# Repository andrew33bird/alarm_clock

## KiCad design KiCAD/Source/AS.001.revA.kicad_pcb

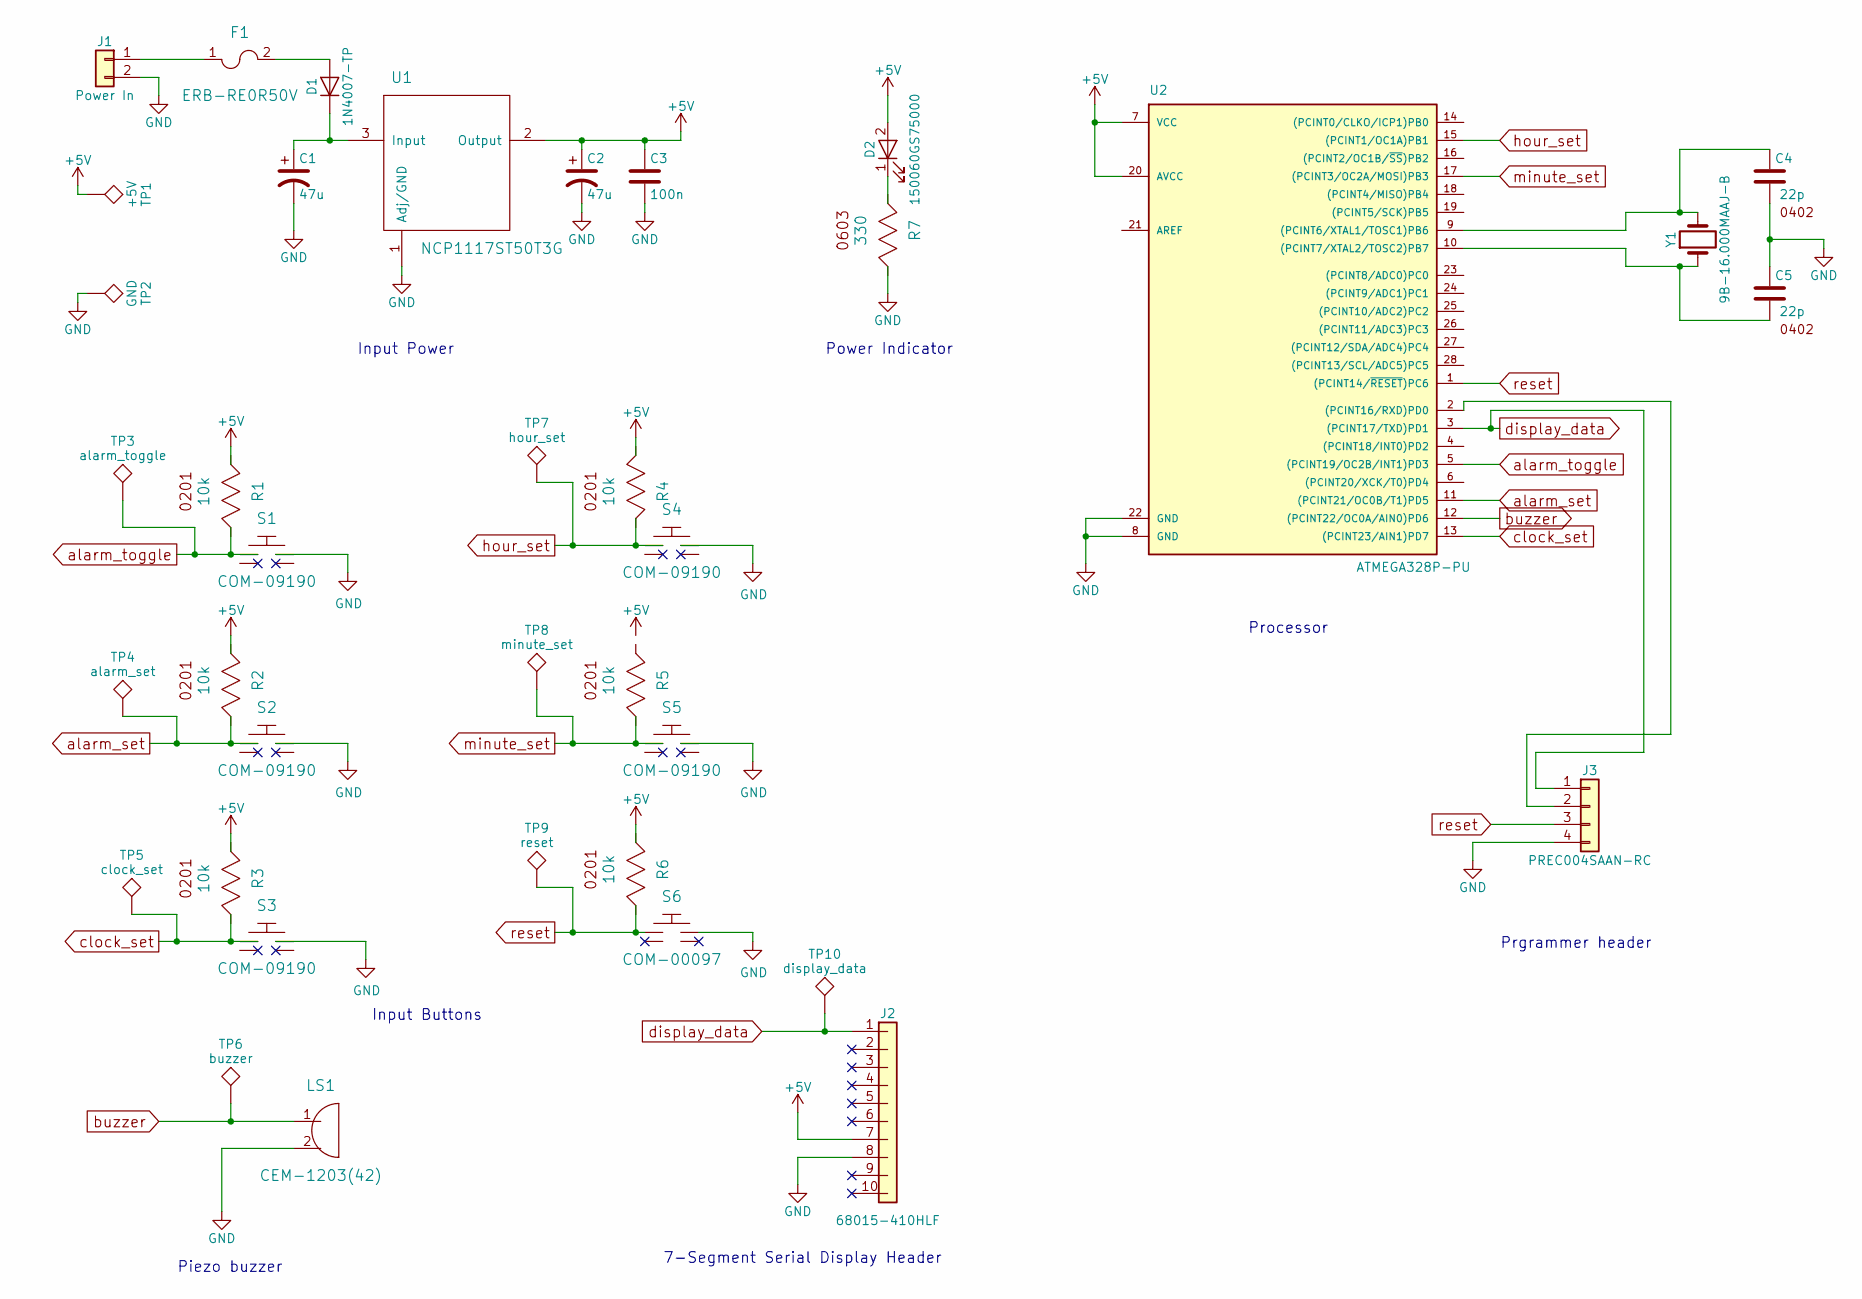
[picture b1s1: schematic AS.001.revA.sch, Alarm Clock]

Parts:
C1, C2: 47u; CP_Radial_D5.0mm_P2.00mm
C3: 100n; C_0603_1608Metric_Pad1.05x0.95mm_HandSolder
C4, C5: 22p; C_0603_1608Metric_Pad1.05x0.95mm_HandSolder
D1: 1N4007-TP; D_DO-41_SOD81_P10.16mm_Horizontal
D2: 150060GS75000; LED_0603_1608Metric_Pad1.05x0.95mm_HandSolder
F1: ERB-RE0R50V; R_0603_1608Metric_Pad1.05x0.95mm_HandSolder
J1: Power In; PinSocket_1x02_P2.54mm_Vertical
J2: 68015-410HLF; PinSocket_1x10_P2.54mm_Horizontal
J3: PREC004SAAN-RC; PinSocket_1x04_P2.54mm_Vertical
LS1: CEM-1203(42)
R1, R2, R3, R4, R5, R6: 10k; R_0603_1608Metric_Pad1.05x0.95mm_HandSolder
R7: 330; R_0603_1608Metric_Pad1.05x0.95mm_HandSolder
S1, S2, S3, S4, S5: COM-09190
S6: COM-00097
TP1: +5V; TestPoint_Plated_Hole_D2.0mm
TP2: GND; TestPoint_Plated_Hole_D2.0mm
TP3: alarm_toggle; TestPoint_Plated_Hole_D2.0mm
TP4: alarm_set; TestPoint_Plated_Hole_D2.0mm
TP5: clock_set; TestPoint_Plated_Hole_D2.0mm
TP6: buzzer; TestPoint_Plated_Hole_D2.0mm
TP7: hour_set; TestPoint_Plated_Hole_D2.0mm
TP8: minute_set; TestPoint_Plated_Hole_D2.0mm
TP9: reset; TestPoint_Plated_Hole_D2.0mm
TP10: display_data; TestPoint_Plated_Hole_D2.0mm
U1: NCP1117ST50T3G; NCP1117ST50T3G (TO-261-4)
U2: ATMEGA328P-PU; DIP-28_W7.62mm
Y1: 9B-16.000MAAJ-B; Crystal_HC49-U_Vertical

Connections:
+5V: C2.1, C3.1, D2.2 (A), J2.7, R1.1 (A), R2.1 (A), R3.1 (A), R4.2 (B), R6.1 (A), TP1.1, U1.2 (Output), U2.7 (VCC), U2.20 (AVCC); also elsewhere on the board
GND: C1.2, C2.2, C3.2, C4.2, C5.1, J1.2, J2.8, J3.4, LS1.2, R7.2 (B), S1.3 (C), S2.3 (C), S3.3 (C), S4.3 (C), S5.3 (C), S6.3 (C), TP2.1, U1.1 (Adj/GND), U2.8 (GND), U2.22 (GND); also elsewhere on the board
unnamed: C1.1, D1.1 (K), U1.3 (Input)
unnamed: C4.1, U2.9 ((PCINT6/XTAL1/TOSC1)PB6), Y1.2
unnamed: C5.2, U2.10 ((PCINT7/XTAL2/TOSC2)PB7), Y1.1
unnamed: D1.2 (A), F1.2
unnamed: D2.1 (K), R7.1 (A)
unnamed: F1.1, J1.1
unnamed: J3.2, U2.2 ((PCINT16/RXD)PD0)
alarm_set: R2.2 (B), S2.1 (A), TP4.1, U2.11 ((PCINT21/OC0B/T1)PD5)
alarm_toggle: R1.2 (B), S1.1 (A), TP3.1, U2.5 ((PCINT19/OC2B/INT1)PD3)
buzzer: LS1.1, TP6.1, U2.12 ((PCINT22/OC0A/AIN0)PD6)
clock_set: R3.2 (B), S3.1 (A), TP5.1, U2.13 ((PCINT23/AIN1)PD7)
display_data: J2.1, J3.1, TP10.1, U2.3 ((PCINT17/TXD)PD1)
hour_set: R4.1 (A), S4.1 (A), TP7.1, U2.15 ((PCINT1/OC1A)PB1)
minute_set: R5.2 (B), S5.1 (A), TP8.1, U2.17 ((PCINT3/OC2A/MOSI)PB3)
reset: J3.3, R6.2 (B), S6.1 (A), TP9.1, U2.1 ((PCINT14/~RESET~)PC6)

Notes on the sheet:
Input Power
Input Buttons
Power Indicator
Piezo buzzer
7-Segment Serial Display Header
Processor
Prgrammer header

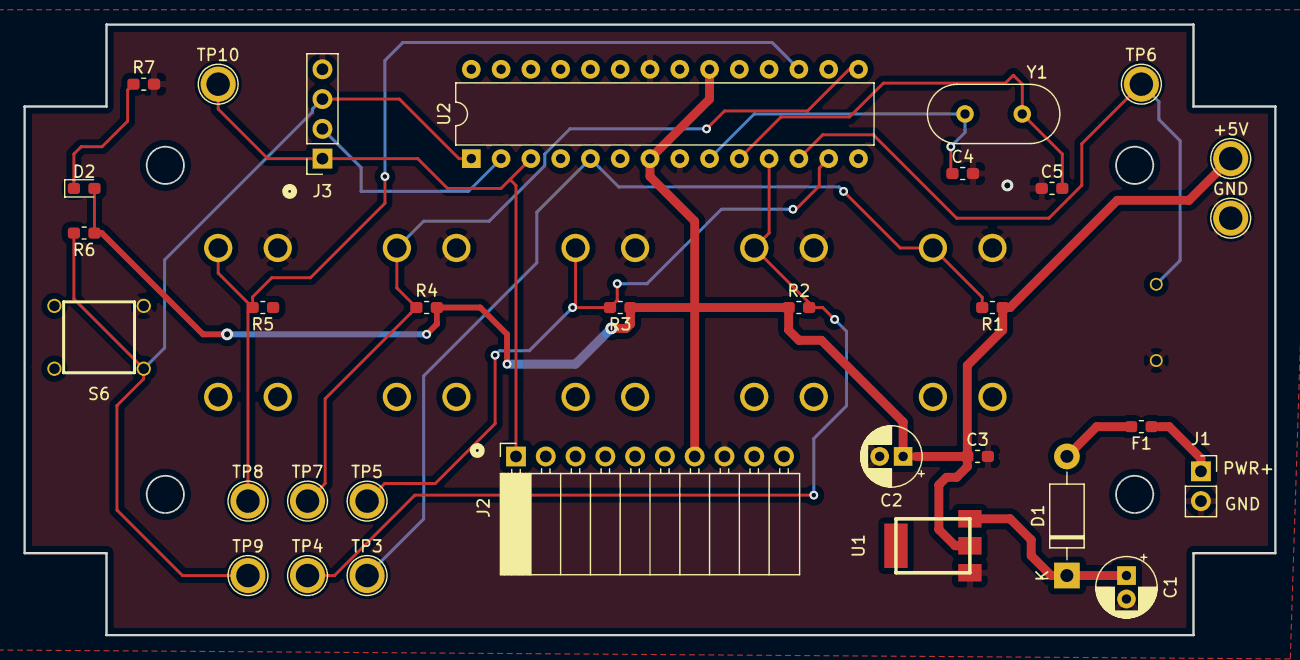
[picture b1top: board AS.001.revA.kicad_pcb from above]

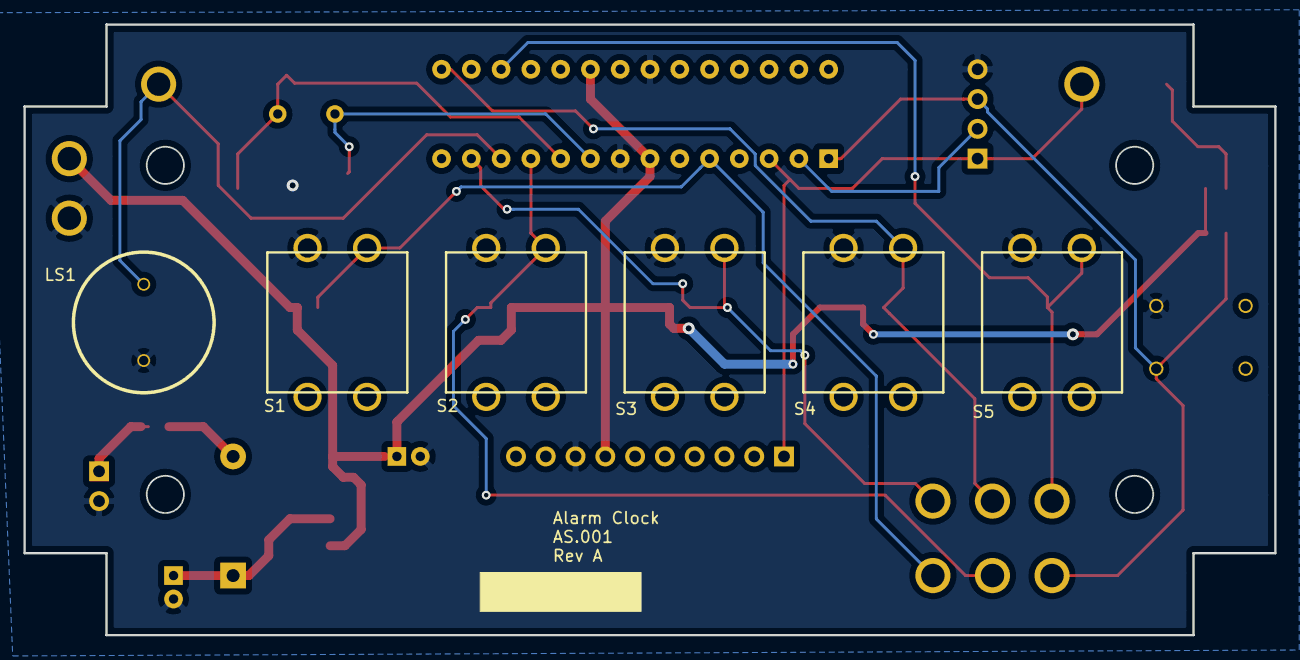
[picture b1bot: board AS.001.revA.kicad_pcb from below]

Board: 2 copper layers, 106.7 x 52.1 mm, 38 parts (6 on the bottom side), 17 nets.

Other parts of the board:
+5V: +5V; TestPoint_Plated_Hole_D2.0mm
GND: GND; TestPoint_Plated_Hole_D2.0mm

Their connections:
+5V: +5V.1; also elsewhere on the board
GND: GND.1; also elsewhere on the board

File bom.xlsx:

Item | Part Number | Qnty | Price (ea) | Price (tot) | Distributor | Link
Microcontroller | ATMEGA328P-PU | 1 | 2.6 | 2.6 | Amazon | https://www.amazon.com/gp/product/B07BZMCK8S/ref=oh_aui_deta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
5V Regulator | NCP1117ST50T3G | 1 | 0.54 | 0.54 | Digikey | https://www.digikey.com/product-detail/en/on-semiconductor/N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
47 uF Capacitor | 860020472006 | 2 | 0.1 | 0.2 | Digikey | https://www.digikey.com/product-detail/en/wurth-electronics-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
Power Diode | 1N4007-TP | 1 | 0.11 | 0.11 | Digikey | https://www.digikey.com/product-detail/en/micro-commercial-c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
100 nF Capacitor | GRM033R61A104ME15D | 1 | 0.1 | 0.1 | Digikey | https://www.digikey.com/product-detail/en/murata-electronics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
16 MHz Crystal | 9B-16.000MAAJ-B | 1 | 0.39 | 0.39 | Digikey | https://www.digikey.com/products/en?keywords=887-1019-ND
22 pF Capacitor | 04025A220JAT2A | 2 | 0.1 | 0.2 | Digikey | https://www.digikey.com/product-detail/en/avx-corporation/04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
Tinted plastic (1/8" x 4" x 4" Sample) | Cast Acrylic - Transparent Colors (Trasparent Light Smoke) | 1 | 2 | 2 | Tap Plastics | https://www.tapplastics.com/product/plastics/plastic_sheets_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
10k Resistor | RMCF0201FT10K0 | 6 | 0.1 | 0.60000000000000009 | Digikey | https://www.digikey.com/product-detail/en/stackpole-electron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
Power LED | 150060GS75000 | 1 | 0.15 | 0.15 | Digikey | https://www.digikey.com/product-detail/en/wurth-electronics-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
330 LED Resistor | CR0603-JW-331ELF | 1 | 0.1 | 0.1 | Digikey | https://www.digikey.com/product-detail/en/bourns-inc/CR0603-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
Programmer header | PREC004SAAN-RC | 1 | 0.12 | 0.12 | Digikey | https://www.digikey.com/product-detail/en/sullins-connector-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
7-Segment Serial Display - Blue | COM-11442 | 1 | 13.95 | 13.95 | Sparkfun | https://www.sparkfun.com/products/11442
10-Segment Right angle header | 68015-410HLF | 1 | 0.45 | 0.45 | Digikey | https://www.digikey.com/product-detail/en/amphenol-icc-fci/6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
Reset push button | COM-00097 | 1 | 0.35 | 0.35 | Sparkfun | https://www.sparkfun.com/products/97
500mA fuse | ERB-RE0R50V | 1 | 0.28999999999999998 | 0.28999999999999998 | Digikey | https://www.digikey.com/product-detail/en/panasonic-electron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
Large pushbutton | COM-09190 | 5 | 0.5 | 2.5 | Sparkfun | https://www.sparkfun.com/products/9190
Mini Piezo Speaker | CEM-1203(42) | 1 | 0.83 | 0.83 | Digikey | https://www.digikey.com/products/en?keywords=CEM-1203
Total |  |  |  | 25.479999999999997

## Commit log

2020-03-28 initial commit - project complete
